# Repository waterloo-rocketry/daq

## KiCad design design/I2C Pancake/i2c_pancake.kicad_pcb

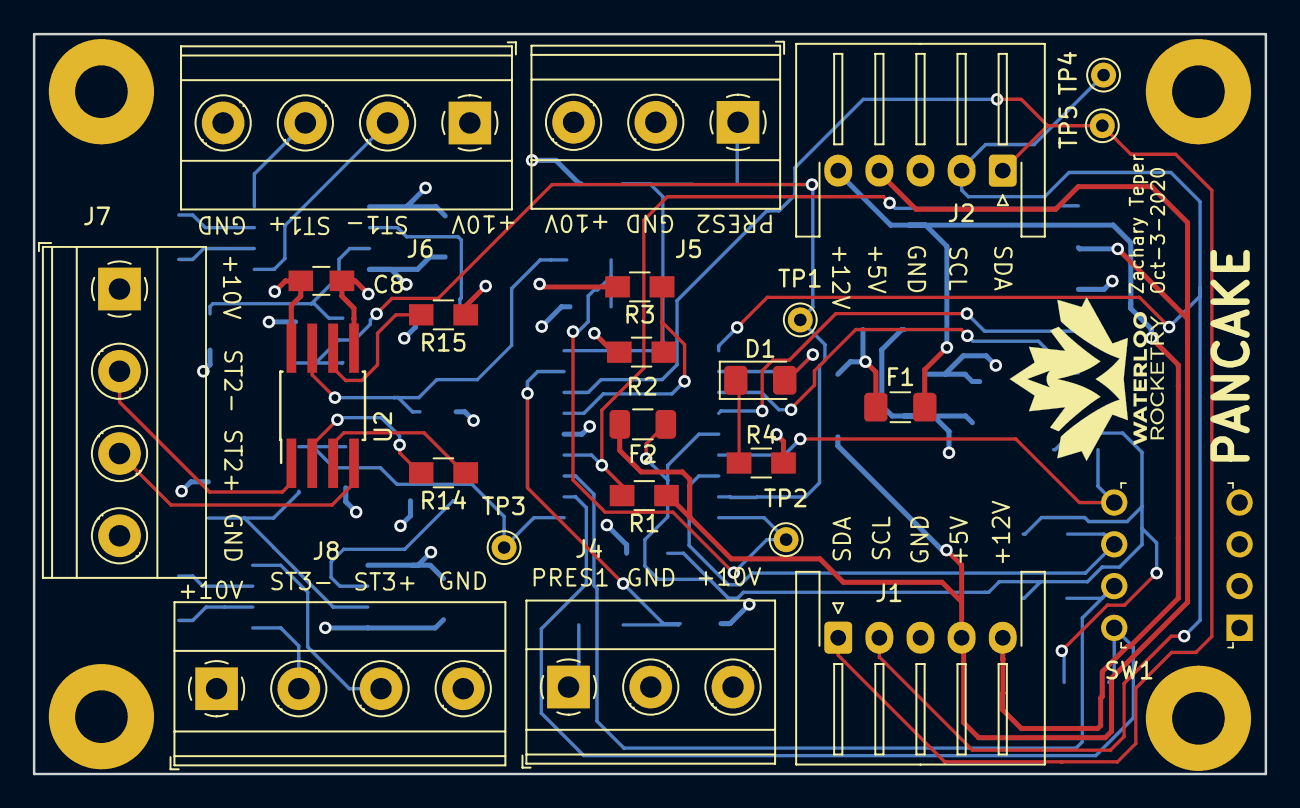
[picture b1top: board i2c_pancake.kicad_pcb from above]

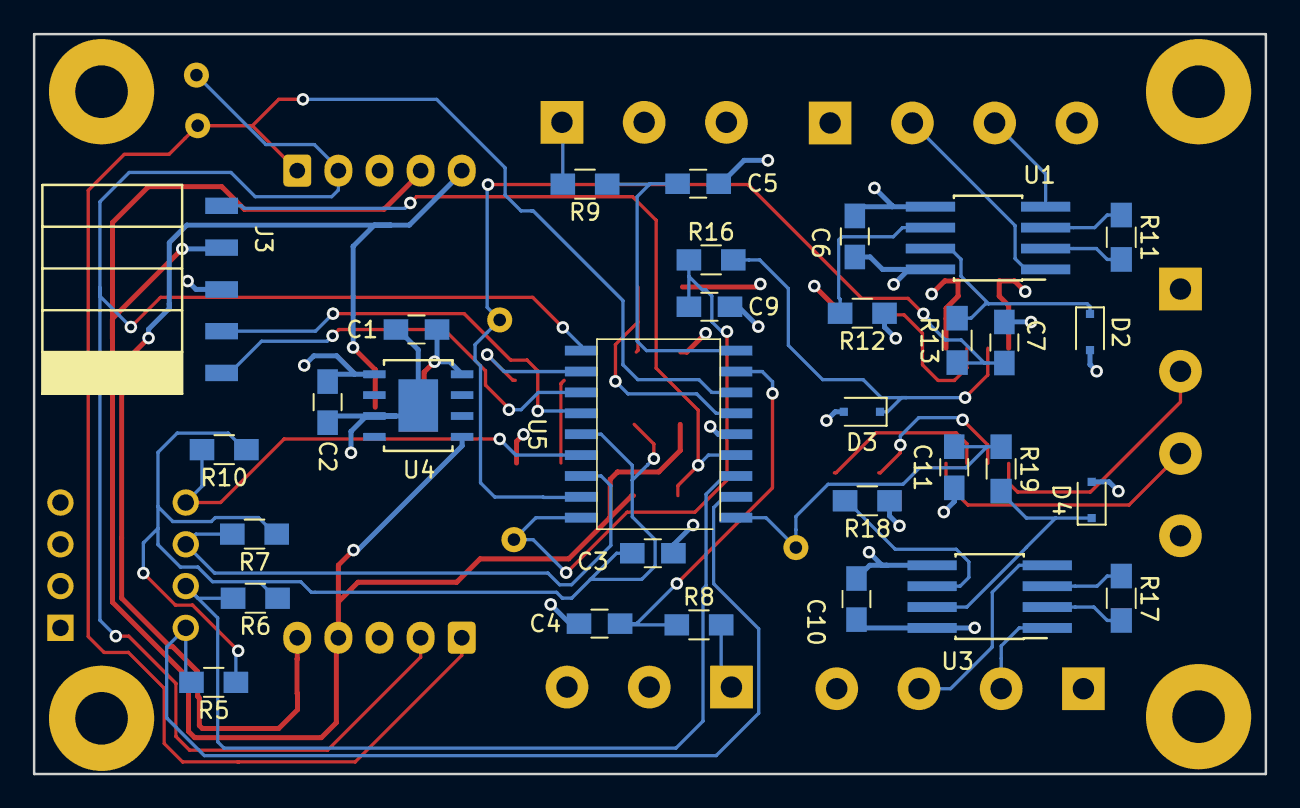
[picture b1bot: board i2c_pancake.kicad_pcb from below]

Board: 4 copper layers, 74.9 x 45.0 mm, 55 parts (31 on the bottom side), 43 nets.

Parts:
C1, C2, C4, C5, C7, C9, C11: 1 uF; C_0805_HandSoldering
C3, C6, C8, C10: 0.1uF; C_0805_HandSoldering
D1: LED; LED_1206_3216Metric_Pad1.42x1.75mm_HandSolder
D2, D3, D4: DDZ4V7ASF-7; D_SOD-323F
F1: Fuse; Fuse_1206_3216Metric_Pad1.42x1.75mm_HandSolder
F2: Fuse; Fuse_1206_3216Metric
J1, J2: Conn_01x05_Male; JST_XH_S5B-XH-A-1_1x05_P2.50mm_Horizontal
J3: Conn_01x05_Female; PinHeader_5x2.54_SMD_90deg_952-3198-1-ND
J4, J5: Conn_01x03; TerminalBlock_Phoenix_MKDS-1,5-3_1x03_P5.00mm_Horizontal
J6, J7, J8: Conn_01x04; TerminalBlock_Phoenix_MKDS-1,5-4_1x04_P5.00mm_Horizontal
R1, R2, R5, R6, R7, R10: 10K; R_0805_HandSoldering
R3: 5K; R_0805_HandSoldering
R4: 330; R_0805_HandSoldering
R8, R9, R13, R16, R19: 150; R_0805_HandSoldering
R11, R14, R17: R; R_0805_HandSoldering
R12, R15, R18: 0; R_0805_HandSoldering
SW1: SW_DIP_x04; DIP_SWITCH_4X2
TP1, TP2, TP3, TP4, TP5: TestPoint
U1, U2, U3: INA826; SOIC-8_3.9x4.9mm_Pitch1.27mm_HandSoldering
U4: BDJ0FC0WEFJ-E2
U5: PIC16F1826-ISO

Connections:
+5V: F2.2, J1.4, J2.4, J3.4, R1.1, U4.5
+10V: C2.1, C6.2, C8.2, C10.2, J4.3, J5.3, J6.1, J7.1, J8.1, R2.1, U1.8, U2.8, U3.8, U4.1
+12V: F1.2, J1.5, J2.5
/DIP_1: R5.2, SW1.8, U5.2
/DIP_2: R6.2, SW1.7, U5.3
/DIP_3: R7.2, SW1.6, U5.16
/DIP_4: R10.2, SW1.5, U5.15
/ICSPCLK: J3.1, U5.12
/ICSPDAT: J3.2, U5.13
/P1_IN: J4.1, R8.2
/P2_IN: J5.1, R9.2
/PRESSURE_1: C4.1, R8.1, U5.8
/PRESSURE_2: C5.1, R9.1, U5.9
/SCL: J1.2, J2.2, TP4.1, U5.10
/SDA: J1.1, J2.1, TP5.1, U5.7
/STRAIN_OUT_1: C7.1, R13.1, TP1.1, U5.17
/STRAIN_OUT_2: C9.1, R16.1, TP2.1, U5.18
/STRAIN_OUT_3: C11.1, R19.1, TP3.1, U5.1
/~MCLR: J3.5, R1.2, U5.4
GND: C1.2, C2.2, C3.1, C4.2, C5.2, C6.1, C7.2, C8.1, C9.2, C10.1, C11.2, D2.2, D3.2, D4.2, J1.3, J2.3, J3.3, J4.2, J5.2, J6.4, J7.4, J8.4, R3.2, R4.2, R12.1, R15.1, R18.1, SW1.1, SW1.2, SW1.3, SW1.4, U1.5, U2.5, U3.5, U4.3, U4.EPAD, U5.5
unnamed: C1.1, F1.1, U4.8
unnamed: D1.1, R4.1
unnamed: D1.2, U5.11
unnamed: D2.1, R13.2, U1.7
unnamed: D3.1, R16.2, U2.7
unnamed: D4.1, R19.2, U3.7
unnamed: J6.2, U1.1
unnamed: J6.3, U1.4
unnamed: J7.2, U2.1
unnamed: J7.3, U2.4
unnamed: J8.2, U3.1
unnamed: J8.3, U3.4
unnamed: R2.2, R3.1, U5.6
unnamed: R11.1, U1.3
unnamed: R11.2, U1.2
unnamed: R12.2, U1.6
unnamed: R14.1, U2.3
unnamed: R14.2, U2.2
unnamed: R15.2, U2.6
unnamed: R17.1, U3.3
unnamed: R17.2, U3.2
unnamed: R18.2, U3.6
VDD: C3.2, F2.1, R5.1, R6.1, R7.1, R10.1, U5.14

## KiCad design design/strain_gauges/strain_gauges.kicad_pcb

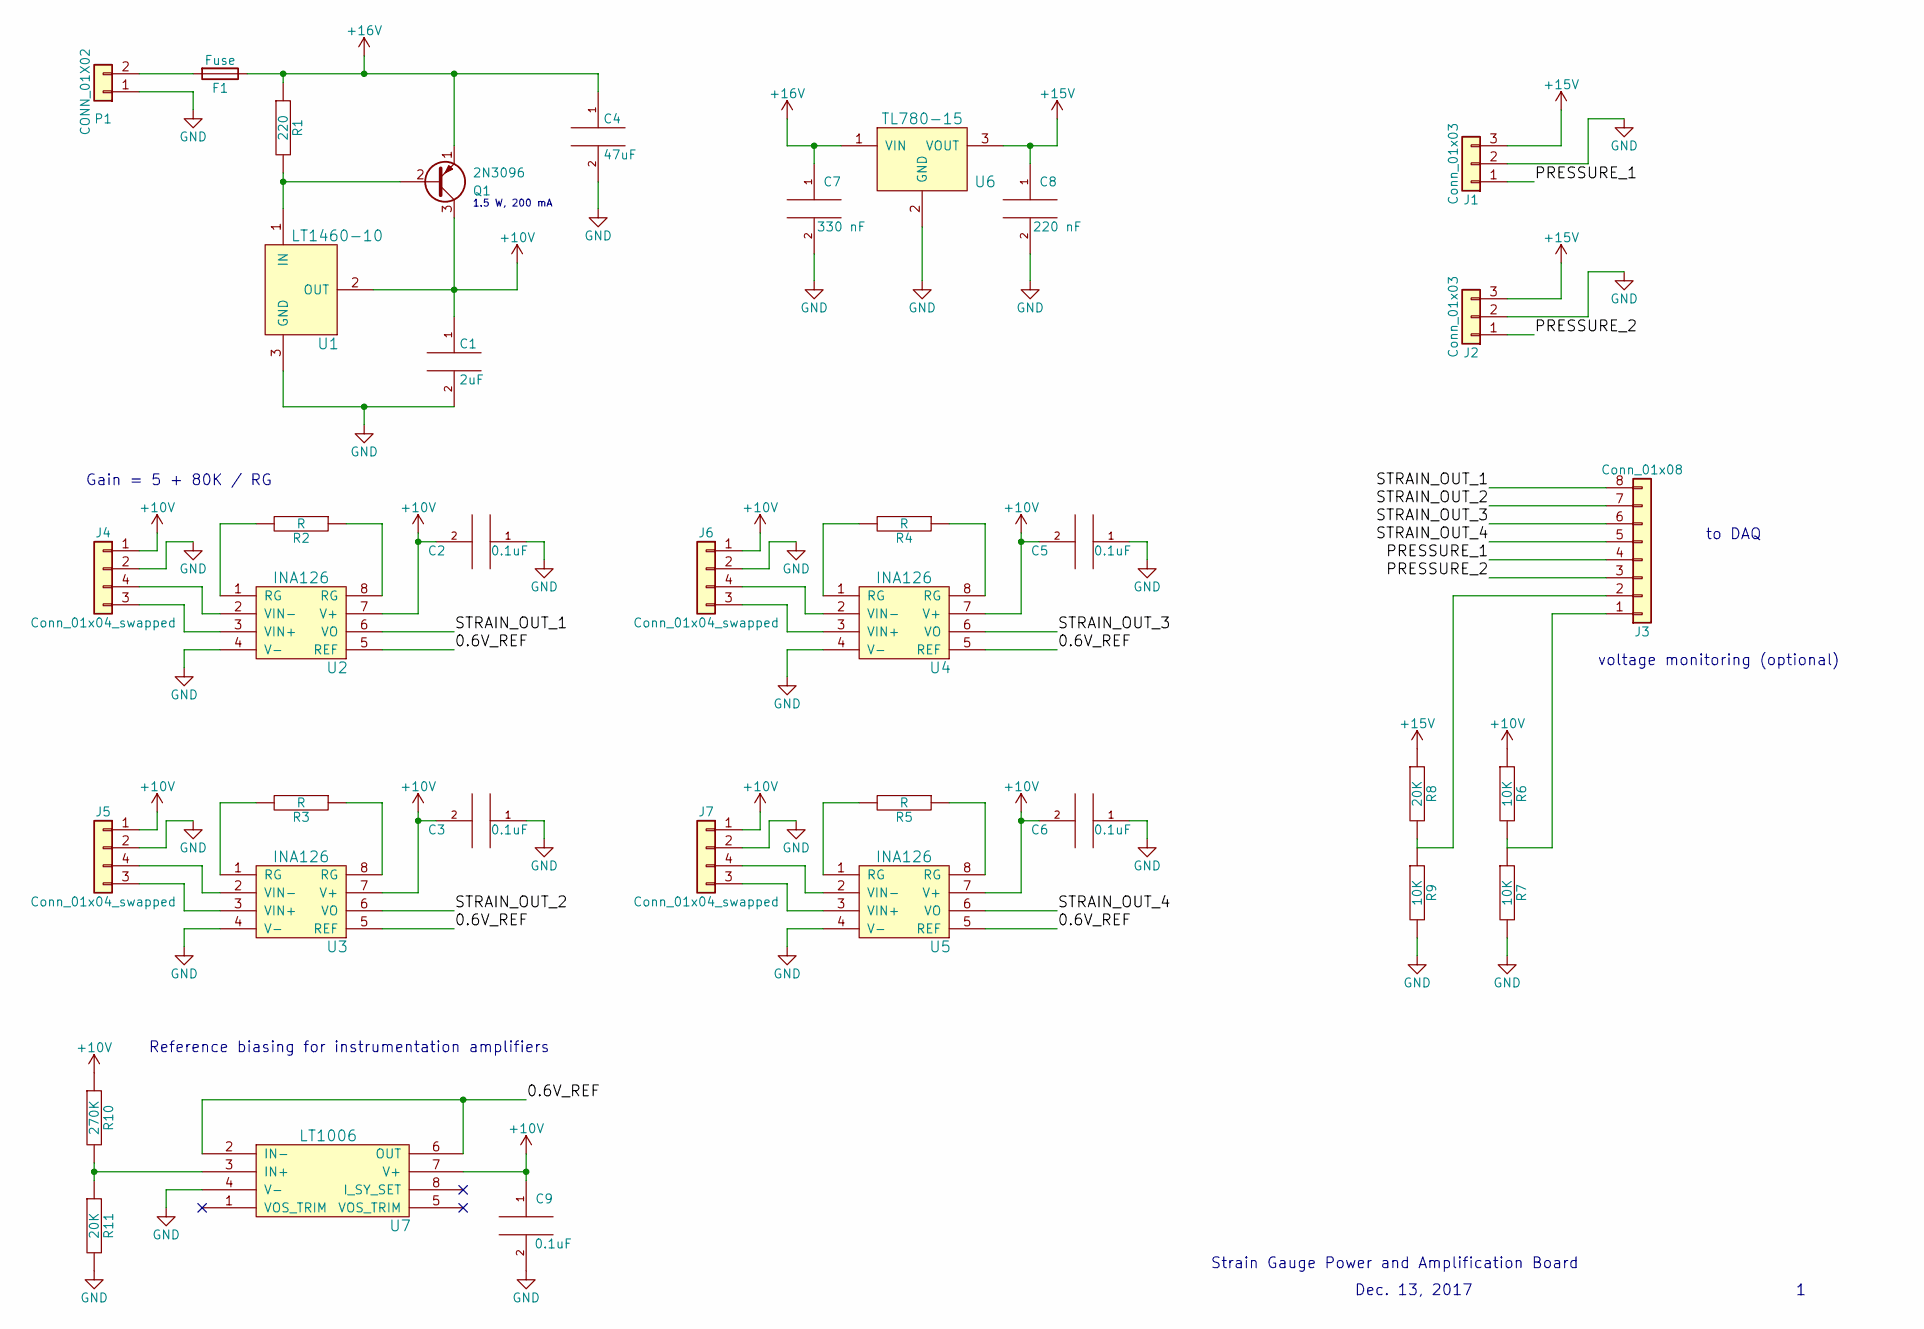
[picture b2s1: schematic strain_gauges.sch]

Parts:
C1: 2uF; CP_Radial_Tantal_D5.0mm_P2.50mm
C2, C3, C5, C6, C9: 0.1uF; C_0805_HandSoldering
C4: 47uF; CP_Radial_Tantal_D6.0mm_P2.50mm
C7: 330 nF; C_0805_HandSoldering
C8: 220 nF; C_0805_HandSoldering
F1: Fuse; Fuse_1206_3216Metric_Pad1.24x1.80mm_HandSolder
J1, J2: Conn_01x03; PhoenixContact_MCV-G_03x3.50mm_Vertical
J3: Conn_01x08; PhoenixContact_MCV-G_08x3.50mm_Vertical
J4, J5, J6, J7: Conn_01x04_swapped; PhoenixContact_MCV-G_04x3.50mm_Vertical
P1: CONN_01X02; PhoenixContact_MCV-G_02x3.50mm_Vertical
Q1: 2N3096; TO-92_Inline_Narrow_Oval
R1: 220; R_0805_HandSoldering
R2, R3, R4, R5: R; R_0805_HandSoldering
R6, R7, R9: 10K; R_0805_HandSoldering
R8, R11: 20K; R_0805_HandSoldering
R10: 270K; R_0805_HandSoldering
U1: LT1460-10; TO-92_Inline_Narrow_Oval
U2, U3, U4, U5: INA126; DIP-8_W7.62mm
U6: TL780-15; TO-220-3_Vertical
U7: LT1006; DIP-8_W7.62mm

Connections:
+10V: C1.1, C2.2, C3.2, C5.2, C6.2, C9.1, J4.1, J5.1, J6.1, J7.1, Q1.3 (C), R6.1, R10.1, U1.2 (OUT), U2.7 (V+), U3.7 (V+), U4.7 (V+), U5.7 (V+), U7.7 (V+)
+15V: C8.1, J1.3, J2.3, R8.1, U6.3 (VOUT)
+16V: C4.1, C7.1, F1.1, Q1.1 (E), R1.1, U6.1 (VIN)
/0.6V_REF: U2.5 (REF), U3.5 (REF), U4.5 (REF), U5.5 (REF), U7.2 (IN-), U7.6 (OUT)
/PRESSURE_1: J1.1, J3.4
/PRESSURE_2: J2.1, J3.3
/STRAIN_OUT_1: J3.8, U2.6 (VO)
/STRAIN_OUT_2: J3.7, U3.6 (VO)
/STRAIN_OUT_3: J3.6, U4.6 (VO)
/STRAIN_OUT_4: J3.5, U5.6 (VO)
GND: C1.2, C2.1, C3.1, C4.2, C5.1, C6.1, C7.2, C8.2, C9.2, J1.2, J2.2, J4.2, J5.2, J6.2, J7.2, P1.1, R7.2, R9.2, R11.2, U1.3 (GND), U2.4 (V-), U3.4 (V-), U4.4 (V-), U5.4 (V-), U6.2 (GND), U7.4 (V-)
unnamed: F1.2, P1.2
unnamed: J3.1, R6.2, R7.1
unnamed: J3.2, R8.2, R9.1
unnamed: J4.3, U2.3 (VIN+)
unnamed: J4.4, U2.2 (VIN-)
unnamed: J5.3, U3.3 (VIN+)
unnamed: J5.4, U3.2 (VIN-)
unnamed: J6.3, U4.3 (VIN+)
unnamed: J6.4, U4.2 (VIN-)
unnamed: J7.3, U5.3 (VIN+)
unnamed: J7.4, U5.2 (VIN-)
unnamed: Q1.2 (B), R1.2, U1.1 (IN)
unnamed: R2.1, U2.8 (RG)
unnamed: R2.2, U2.1 (RG)
unnamed: R3.1, U3.8 (RG)
unnamed: R3.2, U3.1 (RG)
unnamed: R4.1, U4.8 (RG)
unnamed: R4.2, U4.1 (RG)
unnamed: R5.1, U5.8 (RG)
unnamed: R5.2, U5.1 (RG)
unnamed: R10.2, R11.1, U7.3 (IN+)

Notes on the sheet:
Strain Gauge Power and Amplification Board
Dec. 13, 2017
Gain = 5 + 80K / RG
to DAQ
voltage monitoring (optional)
1.5 W, 200 mA
Reference biasing for instrumentation amplifiers

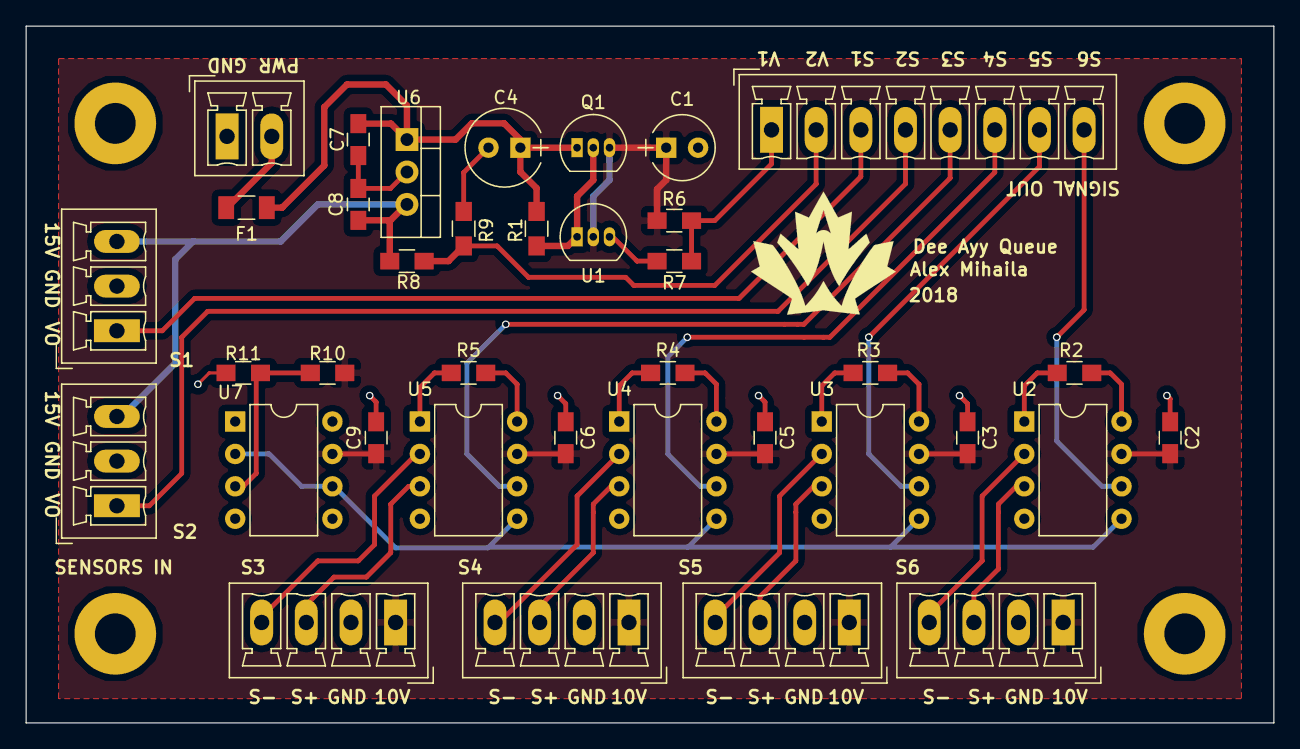
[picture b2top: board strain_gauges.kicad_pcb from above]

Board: 2 copper layers, 97.8 x 54.6 mm, 37 parts (0 on the bottom side), 32 nets.

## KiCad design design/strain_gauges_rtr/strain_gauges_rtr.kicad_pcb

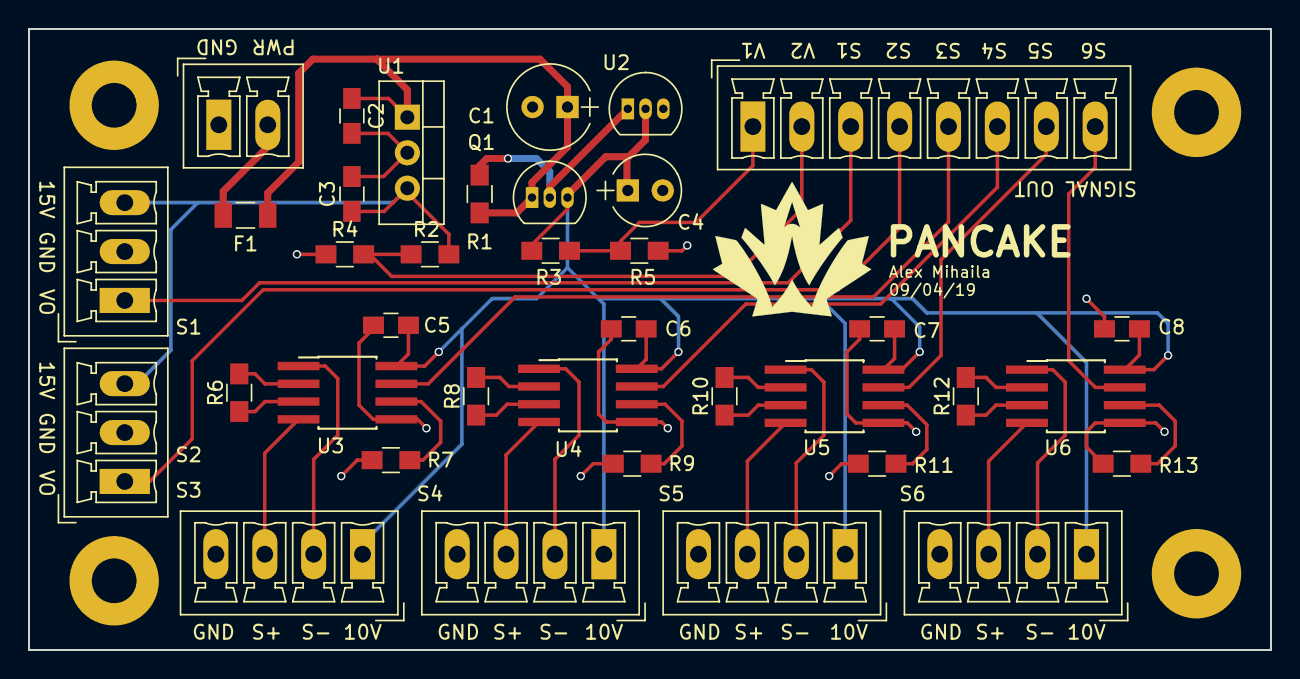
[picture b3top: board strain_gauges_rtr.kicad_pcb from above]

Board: 2 copper layers, 88.9 x 44.5 mm, 37 parts (0 on the bottom side), 34 nets.

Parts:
C1: 47uF; CP_Radial_Tantal_D6.0mm_P2.50mm
C2: 330 nF; C_0805_HandSoldering
C3: 220 nF; C_0805_HandSoldering
C4: 2uF; CP_Radial_Tantal_D5.0mm_P2.50mm
C5, C6, C7, C8: 0.1uF; C_0805_HandSoldering
F1: Fuse; Fuse_1206_3216Metric_Pad1.24x1.80mm_HandSolder
J1, J2: Conn_01x03; PhoenixContact_MCV-G_03x3.50mm_Vertical
J3: Conn_01x08; PhoenixContact_MCV-G_08x3.50mm_Vertical
J4, J5, J6, J7: Conn_01x04; PhoenixContact_MCV-G_04x3.50mm_Vertical
P1: CONN_01X02; PhoenixContact_MCV-G_02x3.50mm_Vertical
Q1: 2N3096; TO-92_Inline_Narrow_Oval
R1: 220; R_0805_HandSoldering
R2: 20K; R_0805_HandSoldering
R3, R4, R5: 10K; R_0805_HandSoldering
R6, R8, R10, R12: R; R_0805_HandSoldering
R7, R9, R11, R13: 0; R_0805_HandSoldering
U1: TL780-15; TO-220-3_Vertical
U2: LT1460-10; TO-92_Inline_Narrow_Oval
U3, U4, U5, U6: INA826; SOIC-8_3.9x4.9mm_Pitch1.27mm_HandSoldering

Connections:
+10V: C4.1, C5.2, C6.2, C7.2, C8.2, J4.1, J5.1, J6.1, J7.1, Q1.3, R3.1, U2.2, U3.8, U4.8, U5.8, U6.8
+15V: C3.1, J1.3, J2.3, R2.1, U1.3
+16V: C1.1, C2.1, F1.1, Q1.1, R1.1, U1.1
/PRESSURE_1: J1.1, J3.3
/PRESSURE_2: J2.1, J3.4
/STRAIN_OUT_1: J3.5, U3.7
/STRAIN_OUT_2: J3.6, U4.7
/STRAIN_OUT_3: J3.7, U5.7
/STRAIN_OUT_4: J3.8, U6.7
GND: C1.2, C2.2, C3.2, C4.2, C5.1, C6.1, C7.1, C8.1, J1.2, J2.2, J4.4, J5.4, J6.4, J7.4, P1.1, R4.2, R5.2, R7.1, R9.1, R11.1, R13.1, U1.2, U2.3, U3.5, U4.5, U5.5, U6.5
unnamed: F1.2, P1.2
unnamed: J3.1, R3.2, R5.1
unnamed: J3.2, R2.2, R4.1
unnamed: J4.2, U3.1
unnamed: J4.3, U3.4
unnamed: J5.2, U4.1
unnamed: J5.3, U4.4
unnamed: J6.2, U5.1
unnamed: J6.3, U5.4
unnamed: J7.2, U6.1
unnamed: J7.3, U6.4
unnamed: Q1.2, R1.2, U2.1
unnamed: R6.1, U3.3
unnamed: R6.2, U3.2
unnamed: R7.2, U3.6
unnamed: R8.1, U4.3
unnamed: R8.2, U4.2
unnamed: R9.2, U4.6
unnamed: R10.1, U5.3
unnamed: R10.2, U5.2
unnamed: R11.2, U5.6
unnamed: R12.1, U6.3
unnamed: R12.2, U6.2
unnamed: R13.2, U6.6

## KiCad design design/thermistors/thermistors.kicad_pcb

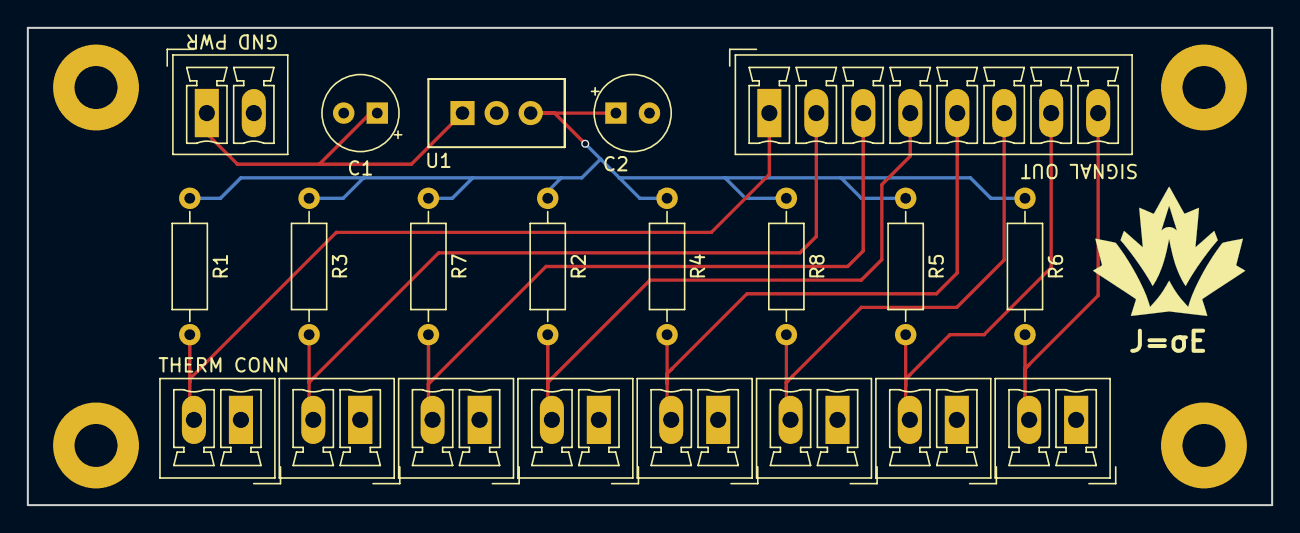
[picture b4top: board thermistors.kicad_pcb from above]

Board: 2 copper layers, 92.7 x 35.6 mm, 21 parts (0 on the bottom side), 11 nets.

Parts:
C1, C2: 10uF; CP_Radial_Tantal_D5.5mm_P2.50mm
J1, J3, J4, J5, J6, J7, J8, J9, J10: Conn_01x02; PhoenixContact_MCV-G_02x3.50mm_Vertical
J2: Conn_01x08; PhoenixContact_MCV-G_08x3.50mm_Vertical
R1, R2, R3, R4, R5, R6, R7, R8: R; R_Axial_DIN0207_L6.3mm_D2.5mm_P10.16mm_Horizontal
U1: R-78E; R-78-converter

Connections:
+5V: C2.1, R1.1, R2.1, R3.1, R4.1, R5.1, R6.1, R7.1, R8.1, U1.3
/16V: C1.1, J1.1, U1.1
/therm_1: J2.1, J3.2, R1.2
/therm_2: J2.2, J5.2, R3.2
/therm_3: J2.3, J9.2, R7.2
/therm_4: J2.4, J4.2, R2.2
/therm_5: J2.5, J6.2, R4.2
/therm_6: J2.6, J10.2, R8.2
/therm_7: J2.7, J7.2, R5.2
/therm_8: J2.8, J8.2, R6.2
GND: C1.2, C2.2, J1.2, J3.1, J4.1, J5.1, J6.1, J7.1, J8.1, J9.1, J10.1, U1.2

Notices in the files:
parts and their libraries:
Copyright 2016 Accelerated Designs. All rights reserved.
